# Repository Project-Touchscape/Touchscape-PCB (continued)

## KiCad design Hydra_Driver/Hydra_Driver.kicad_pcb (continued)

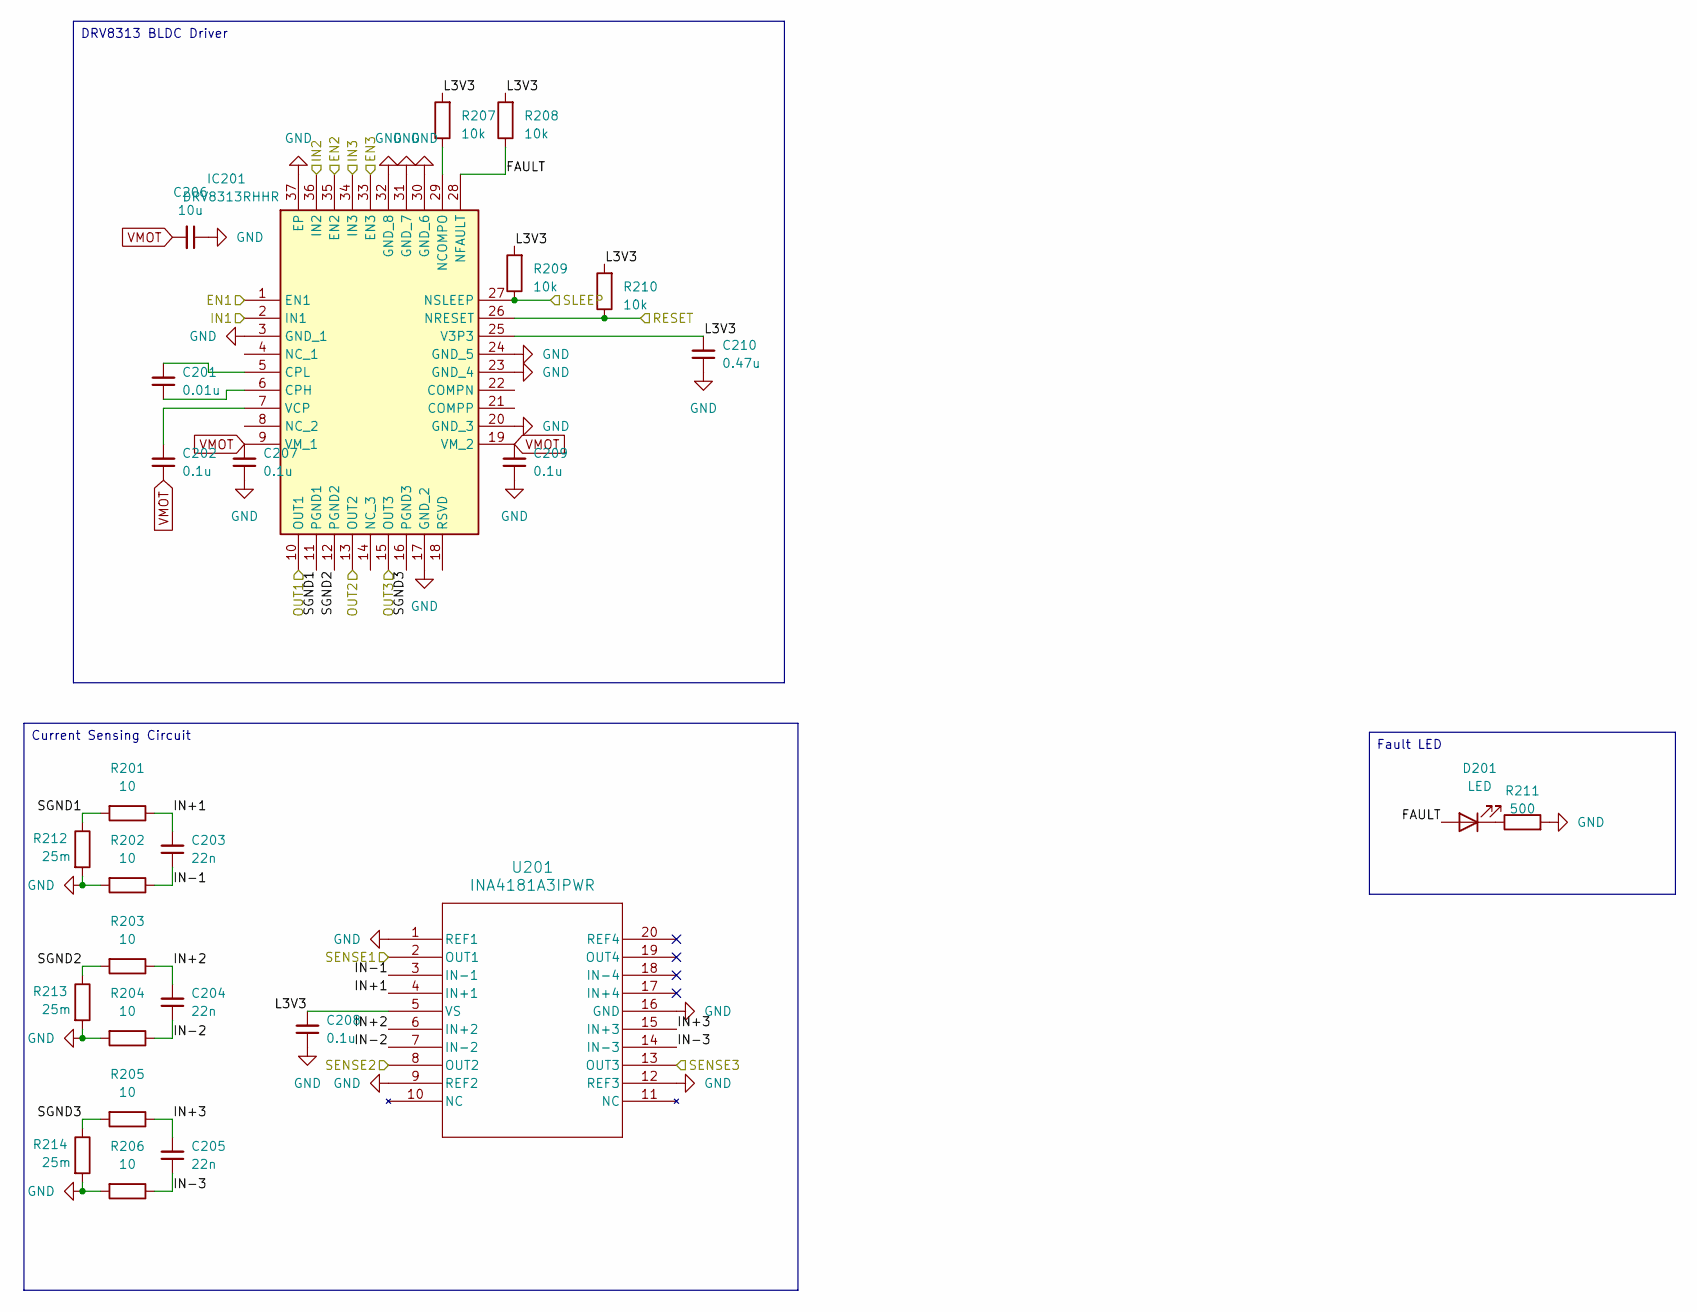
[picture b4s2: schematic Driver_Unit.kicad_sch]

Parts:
C201: 0.01u; C_0402_1005Metric
C202, C207, C208, C209: 0.1u; C_0402_1005Metric
C203, C204, C205: 22n; C_0402_1005Metric
C206: 10u; C_0805_2012Metric
C210: 0.47u; C_0402_1005Metric
D201: LED; LED_0603_1608Metric
IC201: DRV8313RHHR; QFN50P600X600X100-37N-D; Manufacturer_Part_Number DRV8313RHHR; Mouser Part Number 595-DRV8313RHHR
R201, R202, R203, R204, R205, R206: 10; R_0402_1005Metric
R207, R208, R209, R210: 10k; R_0402_1005Metric
R211: 500; R_0402_1005Metric
R212, R213, R214: 25m; R_1206_3216Metric
U201: INA4181A3IPWR; PW20_TEX

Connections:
/Driver_Unit/FAULT: D201.2 (A), IC201.28 (NFAULT), R208.1
/Driver_Unit/IN+1: C203.2, R201.1, U201.4 (IN+1)
/Driver_Unit/IN+2: C204.2, R203.1, U201.6 (IN+2)
/Driver_Unit/IN+3: C205.2, R205.1, U201.15 (IN+3)
/Driver_Unit/IN-1: C203.1, R202.1, U201.3 (IN-1)
/Driver_Unit/IN-2: C204.1, R204.1, U201.7 (IN-2)
/Driver_Unit/IN-3: C205.1, R206.1, U201.14 (IN-3)
/Driver_Unit/L3V3: C208.2, C210.2, IC201.25 (V3P3), R207.2, R208.2, R209.2, R210.2, U201.5 (VS)
/Driver_Unit/SGND1: IC201.11 (PGND1), R201.2, R212.1
/Driver_Unit/SGND2: IC201.12 (PGND2), R203.2, R213.1
/Driver_Unit/SGND3: IC201.16 (PGND3), R205.2, R214.1
/EN1A: IC201.1 (EN1); also elsewhere on the board
/EN2A: IC201.35 (EN2); also elsewhere on the board
/EN3A: IC201.33 (EN3); also elsewhere on the board
/IN1A: IC201.2 (IN1); also elsewhere on the board
/IN2A: IC201.36 (IN2); also elsewhere on the board
/IN3A: IC201.34 (IN3); also elsewhere on the board
/OUT1A: IC201.10 (OUT1); also elsewhere on the board
/OUT2A: IC201.13 (OUT2); also elsewhere on the board
/OUT3A: IC201.15 (OUT3); also elsewhere on the board
/RESET: IC201.26 (NRESET), R210.1; also elsewhere on the board
/SENSE1A: U201.2 (OUT1); also elsewhere on the board
/SENSE2A: U201.8 (OUT2); also elsewhere on the board
/SENSE3A: U201.13 (OUT3); also elsewhere on the board
/SLEEP: IC201.27 (NSLEEP), R209.1; also elsewhere on the board
GND: C206.1, C207.1, C208.1, C209.1, C210.1, IC201.3 (GND_1), IC201.17 (GND_2), IC201.20 (GND_3), IC201.23 (GND_4), IC201.24 (GND_5), IC201.30 (GND_6), IC201.31 (GND_7), IC201.32 (GND_8), IC201.37 (EP), R202.2, R204.2, R206.2, R211.2, R212.2, R213.2, R214.2, U201.1 (REF1), U201.9 (REF2), U201.12 (REF3), U201.16 (GND); also elsewhere on the board
unnamed: D201.1 (K), R211.1
unnamed: C201.1, IC201.6 (CPH)
unnamed: C201.2, IC201.5 (CPL)
unnamed: IC201.29 (NCOMPO), R207.1
unnamed: C202.2, IC201.7 (VCP)
VMOT: C202.1, C206.2, C207.2, C209.2, IC201.9 (VM_1), IC201.19 (VM_2); also elsewhere on the board

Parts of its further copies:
C301: 0.01u; C_0402_1005Metric
C302, C307, C308, C309: 0.1u; C_0402_1005Metric
C303, C304, C305: 22n; C_0402_1005Metric
C306: 10u; C_0805_2012Metric
C310: 0.47u; C_0402_1005Metric
D301: LED; LED_0603_1608Metric
IC301: DRV8313RHHR; QFN50P600X600X100-37N-D; Manufacturer_Part_Number DRV8313RHHR; Mouser Part Number 595-DRV8313RHHR
R301, R302, R303, R304, R305, R306: 10; R_0402_1005Metric
R307, R308, R309, R310: 10k; R_0402_1005Metric
R311: 500; R_0402_1005Metric
R312, R313, R314: 25m; R_1206_3216Metric
U301: INA4181A3IPWR; PW20_TEX

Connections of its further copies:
/Driver_Unit1/FAULT: D301.2 (A), IC301.28 (NFAULT), R308.1
/Driver_Unit1/IN+1: C303.2, R301.1, U301.4 (IN+1)
/Driver_Unit1/IN+2: C304.2, R303.1, U301.6 (IN+2)
/Driver_Unit1/IN+3: C305.2, R305.1, U301.15 (IN+3)
/Driver_Unit1/IN-1: C303.1, R302.1, U301.3 (IN-1)
/Driver_Unit1/IN-2: C304.1, R304.1, U301.7 (IN-2)
/Driver_Unit1/IN-3: C305.1, R306.1, U301.14 (IN-3)
/Driver_Unit1/L3V3: C308.2, C310.2, IC301.25 (V3P3), R307.2, R308.2, R309.2, R310.2, U301.5 (VS)
/Driver_Unit1/SGND1: IC301.11 (PGND1), R301.2, R312.1
/Driver_Unit1/SGND2: IC301.12 (PGND2), R303.2, R313.1
/Driver_Unit1/SGND3: IC301.16 (PGND3), R305.2, R314.1
/EN1B: IC301.1 (EN1); also elsewhere on the board
/EN2B: IC301.35 (EN2); also elsewhere on the board
/EN3B: IC301.33 (EN3); also elsewhere on the board
/IN1B: IC301.2 (IN1); also elsewhere on the board
/IN2B: IC301.36 (IN2); also elsewhere on the board
/IN3B: IC301.34 (IN3); also elsewhere on the board
/OUT1B: IC301.10 (OUT1); also elsewhere on the board
/OUT2B: IC301.13 (OUT2); also elsewhere on the board
/OUT3B: IC301.15 (OUT3); also elsewhere on the board
/RESET: IC301.26 (NRESET), R310.1; also elsewhere on the board
/SENSE1B: U301.2 (OUT1); also elsewhere on the board
/SENSE2B: U301.8 (OUT2); also elsewhere on the board
/SENSE3B: U301.13 (OUT3); also elsewhere on the board
/SLEEP: IC301.27 (NSLEEP), R309.1; also elsewhere on the board
GND: C306.1, C307.1, C308.1, C309.1, C310.1, IC301.3 (GND_1), IC301.17 (GND_2), IC301.20 (GND_3), IC301.23 (GND_4), IC301.24 (GND_5), IC301.30 (GND_6), IC301.31 (GND_7), IC301.32 (GND_8), IC301.37 (EP), R302.2, R304.2, R306.2, R311.2, R312.2, R313.2, R314.2, U301.1 (REF1), U301.9 (REF2), U301.12 (REF3), U301.16 (GND); also elsewhere on the board
unnamed: D301.1 (K), R311.1
unnamed: C301.1, IC301.6 (CPH)
unnamed: C301.2, IC301.5 (CPL)
unnamed: IC301.29 (NCOMPO), R307.1
unnamed: C302.2, IC301.7 (VCP)
VMOT: C302.1, C306.2, C307.2, C309.2, IC301.9 (VM_1), IC301.19 (VM_2); also elsewhere on the board

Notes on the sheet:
DRV8313 BLDC Driver
Fault LED
Current Sensing Circuit

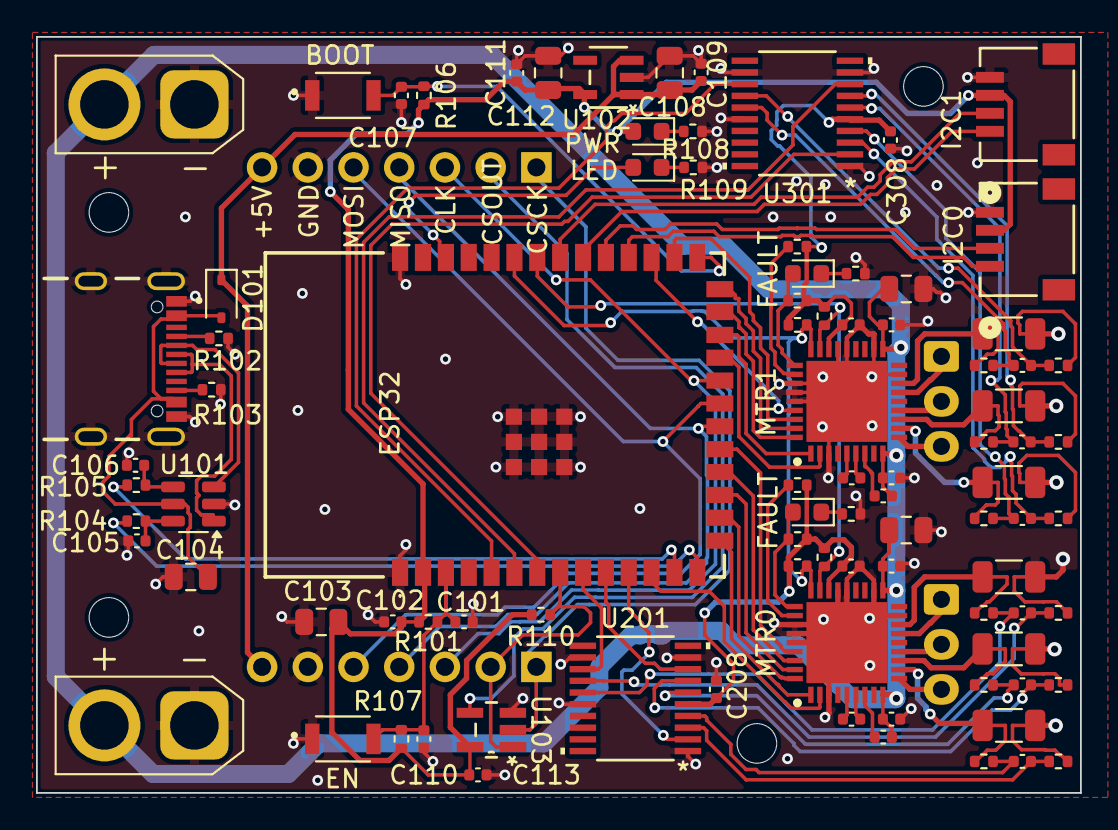
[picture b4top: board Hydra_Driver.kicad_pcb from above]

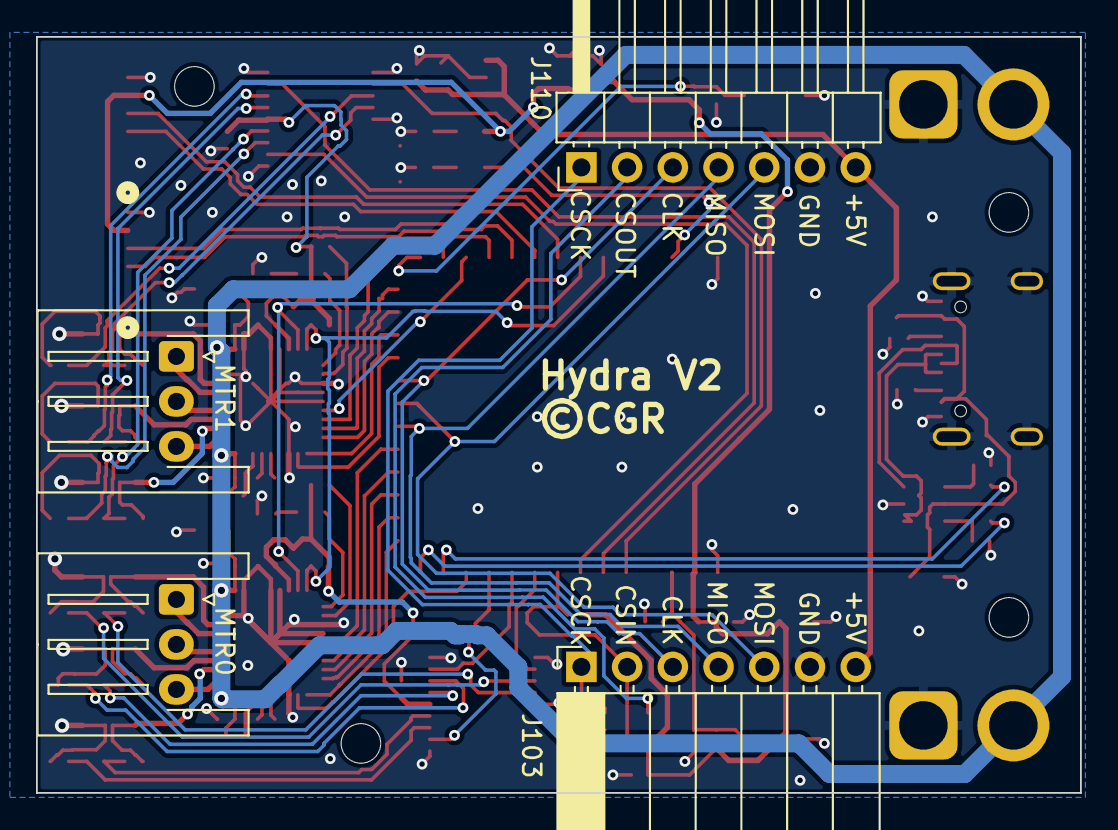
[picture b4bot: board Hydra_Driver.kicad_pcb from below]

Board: 2 copper layers, 58.0 x 42.0 mm, 95 parts (4 on the bottom side), 86 nets.

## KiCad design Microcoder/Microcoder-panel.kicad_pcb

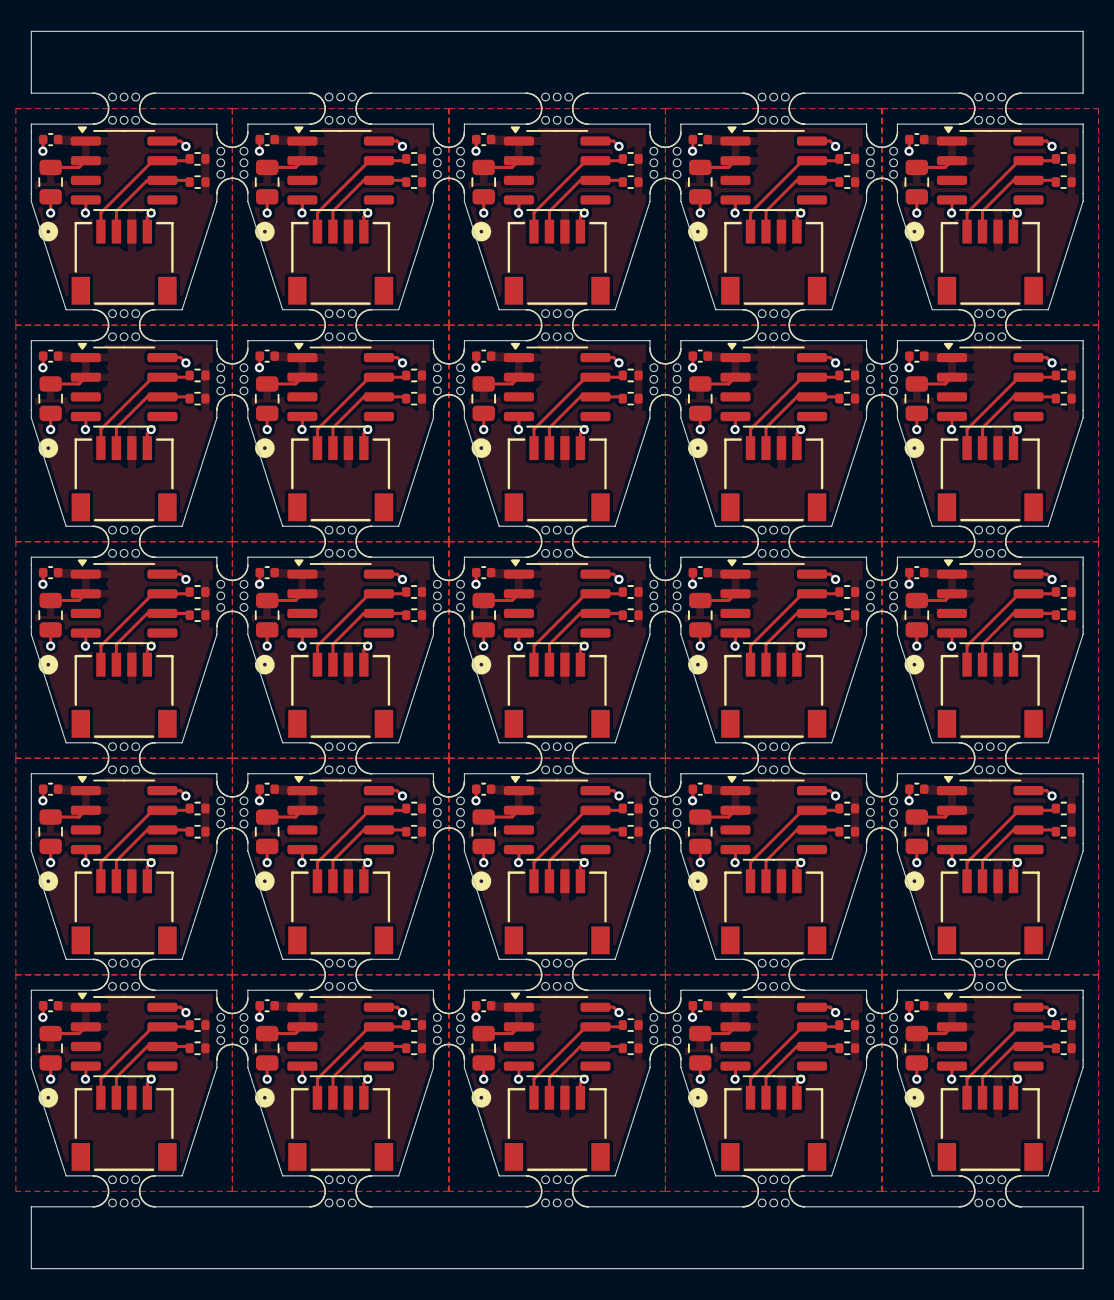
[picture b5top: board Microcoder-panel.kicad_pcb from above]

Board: 2 copper layers, 68.0 x 80.0 mm, 200 parts (0 on the bottom side), 4 nets.

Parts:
C101, C103, C105, C107, C109, C111, C113, C115, C117, C119, C121, C123, C125, C127, C129, C131, C133, C135, C137, C139, C141, C143, C145, C147, C149: 10u; C_0805_2012Metric
C102, C104, C106, C108, C110, C112, C114, C116, C118, C120, C122, C124, C126, C128, C130, C132, C134, C136, C138, C140, C142, C144, C146, C148, C150: 0.1u; C_0402_1005Metric
IC101, IC102, IC103, IC104, IC105, IC106, IC107, IC108, IC109, IC110, IC111, IC112, IC113, IC114, IC115, IC116, IC117, IC118, IC119, IC120, IC121, IC122, IC123, IC124, IC125: AS5600-ASOT; SOIC-8_3.9x4.9mm_P1.27mm
J101, J102, J103, J104, J105, J106, J107, J108, J109, J110, J111, J112, J113, J114, J115, J116, J117, J118, J119, J120, J121, J122, J123, J124, J125: Conn_01x04; CONN_CCSH-W10R-04TR-BK-A_ADA
R101, R102, R103, R104, R105, R106, R107, R108, R109, R110, R111, R112, R113, R114, R115, R116, R117, R118, R119, R120, R121, R122, R123, R124, R125, R126, R127, R128, R129, R130, R131, R132, R133, R134, R135, R136, R137, R138, R139, R140, R141, R142, R143, R144, R145, R146, R147, R148, R149, R150: 10k; R_0402_1005Metric
mouse-bite-2mm-slot, mouse-bite-2mm-slot1, mouse-bite-2mm-slot3, mouse-bite-2mm-slot4, mouse-bite-2mm-slot5, mouse-bite-2mm-slot6, mouse-bite-2mm-slot7, mouse-bite-2mm-slot8, mouse-bite-2mm-slot9, mouse-bite-2mm-slot10, mouse-bite-2mm-slot11, mouse-bite-2mm-slot13, mouse-bite-2mm-slot14, mouse-bite-2mm-slot15, mouse-bite-2mm-slot16, mouse-bite-2mm-slot17, mouse-bite-2mm-slot18, mouse-bite-2mm-slot19, mouse-bite-2mm-slot20, mouse-bite-2mm-slot21, mouse-bite-2mm-slot23, mouse-bite-2mm-slot24, mouse-bite-2mm-slot25, mouse-bite-2mm-slot26, mouse-bite-2mm-slot27, mouse-bite-2mm-slot28, mouse-bite-2mm-slot29, mouse-bite-2mm-slot30, mouse-bite-2mm-slot31, mouse-bite-2mm-slot33, mouse-bite-2mm-slot34, mouse-bite-2mm-slot35, mouse-bite-2mm-slot36, mouse-bite-2mm-slot37, mouse-bite-2mm-slot38, mouse-bite-2mm-slot39, mouse-bite-2mm-slot40, mouse-bite-2mm-slot41, mouse-bite-2mm-slot41#2, mouse-bite-2mm-slot43, mouse-bite-2mm-slot43#2, mouse-bite-2mm-slot44, mouse-bite-2mm-slot45, mouse-bite-2mm-slot45#2, mouse-bite-2mm-slot46, mouse-bite-2mm-slot47, mouse-bite-2mm-slot47#2, mouse-bite-2mm-slot48, mouse-bite-2mm-slot#2, mouse-bite-2mm-slot#3: VAL**; mouse-bite-2mm-slot

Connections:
+3.3V: C101.1, C102.1, C103.1, C104.1, C105.1, C106.1, C107.1, C108.1, C109.1, C110.1, C111.1, C112.1, C113.1, C114.1, C115.1, C116.1, C117.1, C118.1, C119.1, C120.1, C121.1, C122.1, C123.1, C124.1, C125.1, C126.1, C127.1, C128.1, C129.1, C130.1, C131.1, C132.1, C133.1, C134.1, C135.1, C136.1, C137.1, C138.1, C139.1, C140.1, C141.1, C142.1, C143.1, C144.1, C145.1, C146.1, C147.1, C148.1, C149.1, C150.1, IC101.1 (VDD5V), IC101.2 (VDD3V3), IC102.1 (VDD5V), IC102.2 (VDD3V3), IC103.1 (VDD5V), IC103.2 (VDD3V3), IC104.1 (VDD5V), IC104.2 (VDD3V3), IC105.1 (VDD5V), IC105.2 (VDD3V3), IC106.1 (VDD5V), IC106.2 (VDD3V3), IC107.1 (VDD5V), IC107.2 (VDD3V3), IC108.1 (VDD5V), IC108.2 (VDD3V3), IC109.1 (VDD5V), IC109.2 (VDD3V3), IC110.1 (VDD5V), IC110.2 (VDD3V3), IC111.1 (VDD5V), IC111.2 (VDD3V3), IC112.1 (VDD5V), IC112.2 (VDD3V3), IC113.1 (VDD5V), IC113.2 (VDD3V3), IC114.1 (VDD5V), IC114.2 (VDD3V3), IC115.1 (VDD5V), IC115.2 (VDD3V3), IC116.1 (VDD5V), IC116.2 (VDD3V3), IC117.1 (VDD5V), IC117.2 (VDD3V3), IC118.1 (VDD5V), IC118.2 (VDD3V3), IC119.1 (VDD5V), IC119.2 (VDD3V3), IC120.1 (VDD5V), IC120.2 (VDD3V3), IC121.1 (VDD5V), IC121.2 (VDD3V3), IC122.1 (VDD5V), IC122.2 (VDD3V3), IC123.1 (VDD5V), IC123.2 (VDD3V3), IC124.1 (VDD5V), IC124.2 (VDD3V3), IC125.1 (VDD5V), IC125.2 (VDD3V3), J101.3, J102.3, J103.3, J104.3, J105.3, J106.3, J107.3, J108.3, J109.3, J110.3, J111.3, J112.3, J113.3, J114.3, J115.3, J116.3, J117.3, J118.3, J119.3, J120.3, J121.3, J122.3, J123.3, J124.3, J125.3, R101.1, R102.1, R103.1, R104.1, R105.1, R106.1, R107.1, R108.1, R109.1, R110.1, R111.1, R112.1, R113.1, R114.1, R115.1, R116.1, R117.1, R118.1, R119.1, R120.1, R121.1, R122.1, R123.1, R124.1, R125.1, R126.1, R127.1, R128.1, R129.1, R130.1, R131.1, R132.1, R133.1, R134.1, R135.1, R136.1, R137.1, R138.1, R139.1, R140.1, R141.1, R142.1, R143.1, R144.1, R145.1, R146.1, R147.1, R148.1, R149.1, R150.1
/SCL: IC101.7 (SCL), IC102.7 (SCL), IC103.7 (SCL), IC104.7 (SCL), IC105.7 (SCL), IC106.7 (SCL), IC107.7 (SCL), IC108.7 (SCL), IC109.7 (SCL), IC110.7 (SCL), IC111.7 (SCL), IC112.7 (SCL), IC113.7 (SCL), IC114.7 (SCL), IC115.7 (SCL), IC116.7 (SCL), IC117.7 (SCL), IC118.7 (SCL), IC119.7 (SCL), IC120.7 (SCL), IC121.7 (SCL), IC122.7 (SCL), IC123.7 (SCL), IC124.7 (SCL), IC125.7 (SCL), J101.1, J102.1, J103.1, J104.1, J105.1, J106.1, J107.1, J108.1, J109.1, J110.1, J111.1, J112.1, J113.1, J114.1, J115.1, J116.1, J117.1, J118.1, J119.1, J120.1, J121.1, J122.1, J123.1, J124.1, J125.1, R102.2, R104.2, R106.2, R108.2, R110.2, R112.2, R114.2, R116.2, R118.2, R120.2, R122.2, R124.2, R126.2, R128.2, R130.2, R132.2, R134.2, R136.2, R138.2, R140.2, R142.2, R144.2, R146.2, R148.2, R150.2
/SDA: IC101.6 (SDA), IC102.6 (SDA), IC103.6 (SDA), IC104.6 (SDA), IC105.6 (SDA), IC106.6 (SDA), IC107.6 (SDA), IC108.6 (SDA), IC109.6 (SDA), IC110.6 (SDA), IC111.6 (SDA), IC112.6 (SDA), IC113.6 (SDA), IC114.6 (SDA), IC115.6 (SDA), IC116.6 (SDA), IC117.6 (SDA), IC118.6 (SDA), IC119.6 (SDA), IC120.6 (SDA), IC121.6 (SDA), IC122.6 (SDA), IC123.6 (SDA), IC124.6 (SDA), IC125.6 (SDA), J101.2, J102.2, J103.2, J104.2, J105.2, J106.2, J107.2, J108.2, J109.2, J110.2, J111.2, J112.2, J113.2, J114.2, J115.2, J116.2, J117.2, J118.2, J119.2, J120.2, J121.2, J122.2, J123.2, J124.2, J125.2, R101.2, R103.2, R105.2, R107.2, R109.2, R111.2, R113.2, R115.2, R117.2, R119.2, R121.2, R123.2, R125.2, R127.2, R129.2, R131.2, R133.2, R135.2, R137.2, R139.2, R141.2, R143.2, R145.2, R147.2, R149.2
GND: C101.2, C102.2, C103.2, C104.2, C105.2, C106.2, C107.2, C108.2, C109.2, C110.2, C111.2, C112.2, C113.2, C114.2, C115.2, C116.2, C117.2, C118.2, C119.2, C120.2, C121.2, C122.2, C123.2, C124.2, C125.2, C126.2, C127.2, C128.2, C129.2, C130.2, C131.2, C132.2, C133.2, C134.2, C135.2, C136.2, C137.2, C138.2, C139.2, C140.2, C141.2, C142.2, C143.2, C144.2, C145.2, C146.2, C147.2, C148.2, C149.2, C150.2, IC101.4 (GND), IC101.8 (DIR), IC102.4 (GND), IC102.8 (DIR), IC103.4 (GND), IC103.8 (DIR), IC104.4 (GND), IC104.8 (DIR), IC105.4 (GND), IC105.8 (DIR), IC106.4 (GND), IC106.8 (DIR), IC107.4 (GND), IC107.8 (DIR), IC108.4 (GND), IC108.8 (DIR), IC109.4 (GND), IC109.8 (DIR), IC110.4 (GND), IC110.8 (DIR), IC111.4 (GND), IC111.8 (DIR), IC112.4 (GND), IC112.8 (DIR), IC113.4 (GND), IC113.8 (DIR), IC114.4 (GND), IC114.8 (DIR), IC115.4 (GND), IC115.8 (DIR), IC116.4 (GND), IC116.8 (DIR), IC117.4 (GND), IC117.8 (DIR), IC118.4 (GND), IC118.8 (DIR), IC119.4 (GND), IC119.8 (DIR), IC120.4 (GND), IC120.8 (DIR), IC121.4 (GND), IC121.8 (DIR), IC122.4 (GND), IC122.8 (DIR), IC123.4 (GND), IC123.8 (DIR), IC124.4 (GND), IC124.8 (DIR), IC125.4 (GND), IC125.8 (DIR), J101.4, J102.4, J103.4, J104.4, J105.4, J106.4, J107.4, J108.4, J109.4, J110.4, J111.4, J112.4, J113.4, J114.4, J115.4, J116.4, J117.4, J118.4, J119.4, J120.4, J121.4, J122.4, J123.4, J124.4, J125.4
